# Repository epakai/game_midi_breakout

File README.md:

# Game Midi Breakout

This is my compact hobbyist design for converting game port (DB-15) to MIDI ports. It's made in Kicad. The PCB fits inside a [GOLD-TEK/GTK DH151 connector housing](https://www.taydaelectronics.com/connectors-sockets/d-sub-connectors/d-sub-cover-15-pins-with-short-screw.html).

** Note: This revision is untested. **

The previous revision had incorrect transistor pinouts, but I was able to verify its functionality with a bodge (upside-down transistors). This rev has had minor mods to schematic, and a near-complete re-layout. You're taking a chance I messed something up if you build it without verifying.

Here's what I changed: 

- Schematic
    + Swapped 2N3904 for the correct MMBT3904 transistor (corrects pinout)
    + added capacitors to ground the MIDI cable shield

- PCB layout
    + Caps/Resistors lined up, real nice
    + Silkscreen labels for component references
    + Everything but the OptoIsolator moved around and rerouted

## Pictures

### What you get 

### My first attempt with all it's warts

### 3D renders with most of the components

## BOM

| Quantity | Ref(s) | Value | Mfg Part No. | Description |
|----------|--------|-------|--------------|-------------|
| 1 | J5 | - | DA15PT | GTK 15-pin male D-Sub connector |
| 1 | -  | - | DH151PS/RH | GTK 15-pin D-sub cover |
| 1 | U1 | - | 6N138S | Opto-Isolator 5KV Darl w/Base 8SMD |
| 2 | Q1, Q2 | - | MMBT3904 | NPN Transistor 40V 0.2A SOT23-3 | 
| 1 | D1 | - | 1N4148WSTR | Diode 75V 300MA SOD323 | 
| 3 | C1,C4,C5 | 0.1 µF | CL21F104ZBCNNNC | Ceramic Capacitor 50V 0805 |
| 2 | C2,C3 | 220 pF | CL21B221KBANNNC | Ceramic Capacitor 50V 0805 | 
| 2 | R1, R6 | 220 Ω | CR0805-JW-221ELF | SMD Resistor 5% 1/8W 0805 | 
| 1 | R5 | 270 Ω | CR0805-JW-271ELF | SMD Resistor 5% 1/8W 0805 | 
| 2 | R2, R4 | 2.2 KΩ | CR0805-FX-2201ELF | SMD Resistor 1% 1/8W 0805 | 
| 2 | R3 | 10 KΩ | CR0805-JW-103ELF | SMD Resistor 5% 1/8W 0805 | 

Not included are any cables or MIDI connectors. Be creative. You can connect a pair of cables straight to male or female connectors, or run a single cable to a breakout box with a pair of connectors. Just connect IN or OUT if you like, etc.

## Making it

The D-Sub connector has to be modified before soldering. 

- Remove pins 6 and 7. Small pliers work well, wiggle and pull from the back.
- Pins 5 and 8 need to be cut short to make room for the opto-isolator, but you might wait until after U1 is soldered to check the sizing.

Assembly order:
- D1, Q1, Q2
- C1-C3, R1-R6
- C4, C5
- U1
- Remove and cut pins on J5 (15-pin connector) as described above
- J5
- Attach whatever MIDI cable/sockets you prefer

## The Design

The Output circuit comes from [ESS ES1869 Data Sheet, Page 24](https://www.philscomputerlab.com/uploads/3/7/2/3/37231621/es1869techmanual.pdf#page=24).

The Input circuit is similar, but I found the reference at [Teragon Audio](http://midi.teragonaudio.com/hardware/pc_intfc.htm) to be useful, and I took values and components from there.

The PCB is designed to be a close fit inside the connector housing. Rev 1.0 versions I produced at JLCPCB fit well in my initial build.

## Testing

I tested the adapter with a BTC 1853 Card (ES1868F chipset). I was able to transmit and recieve with a MidiMan MidiSport 1x1 USB adaptor. I also transmitted to a Roland MT-90s.

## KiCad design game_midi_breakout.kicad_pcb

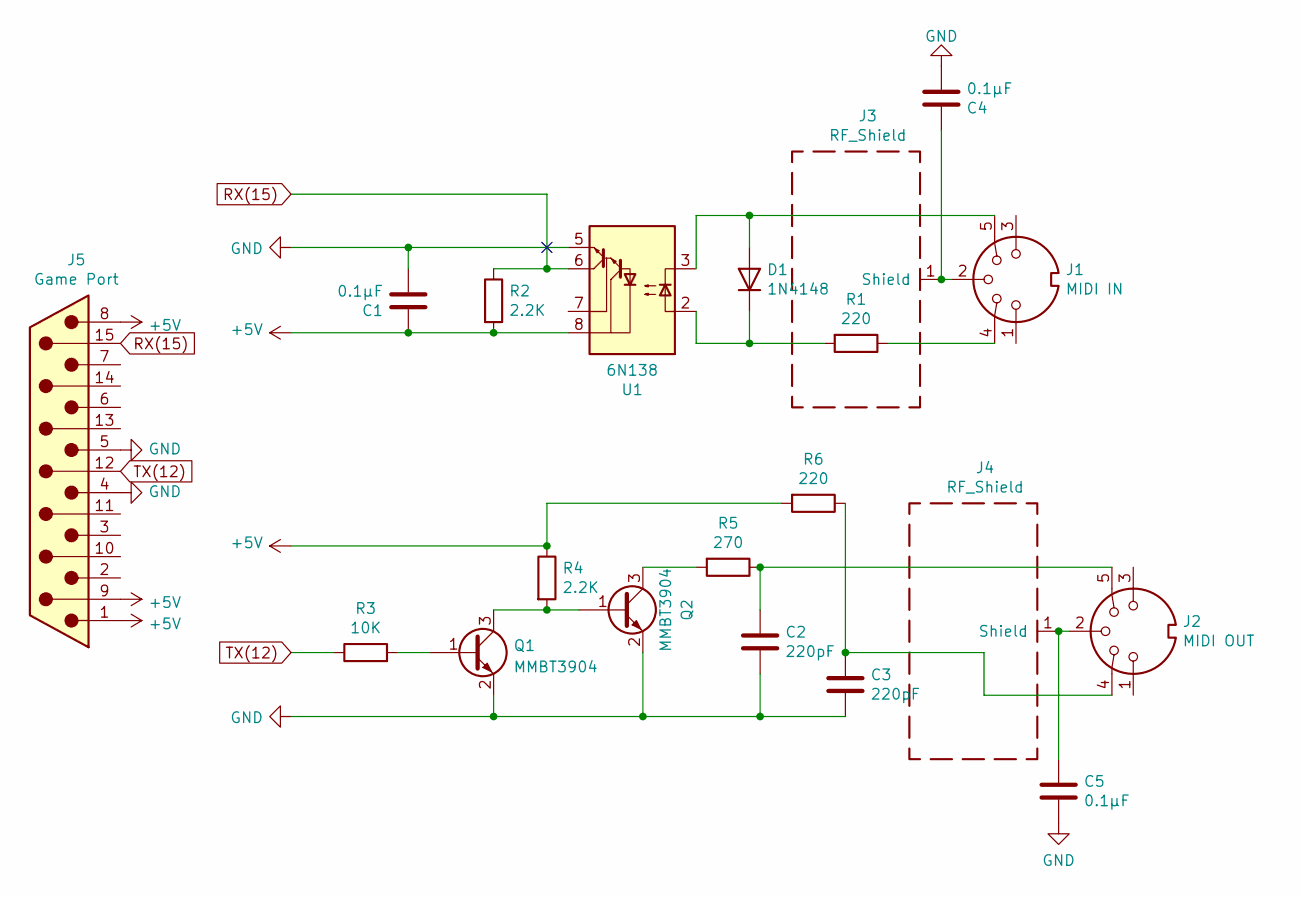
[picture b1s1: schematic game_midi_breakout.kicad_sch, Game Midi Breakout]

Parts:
C1, C4, C5: 0.1μF; C_0805_2012Metric
C2, C3: 220pF; C_0805_2012Metric
D1: 1N4148; D_SOD-323
J1: MIDI IN; midi pads
J2: MIDI OUT; midi pads
J3, J4: RF_Shield
J5: Game Port; DSUB-15_Male_EdgeMount_P2.77mm
Q1, Q2: MMBT3904; SOT-23
R1, R6: 220; R_0805_2012Metric
R2, R4: 2.2K; R_0805_2012Metric
R3: 10K; R_0805_2012Metric
R5: 270; R_0805_2012Metric
U1: 6N138; SMDIP-8_W7.62mm

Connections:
+5V: C1.1, J5.1, J5.8, J5.9, R2.2, R4.1, R6.2, U1.8 (VCC)
GND: C1.2, C2.2, C3.2, C4.2, C5.2, J5.4, J5.5, Q1.2 (E), Q2.2 (E), U1.5 (GND)
unnamed: C2.1, J2.5, R5.1
unnamed: C3.1, J2.4, R6.1
unnamed: D1.1 (K), R1.2, U1.2 (C1)
unnamed: D1.2 (A), J1.5, U1.3 (C2)
unnamed: C4.1, J1.2, J3.1
unnamed: J1.4, R1.1
unnamed: C5.1, J2.2, J4.1
unnamed: Q1.3 (C), Q2.1 (B), R4.2
unnamed: Q1.1 (B), R3.2
unnamed: Q2.3 (C), R5.2
RX(15): J5.15, R2.1, U1.6 (VO2)
TX(12): J5.12, R3.1

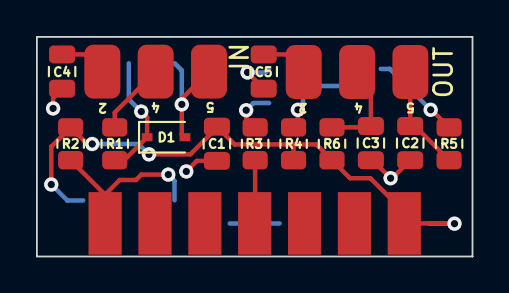
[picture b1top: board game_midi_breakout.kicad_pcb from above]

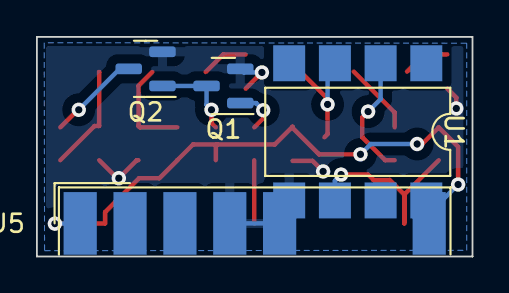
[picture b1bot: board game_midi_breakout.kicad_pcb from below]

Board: 2 copper layers, 24.2 x 12.2 mm, 18 parts (4 on the bottom side), 14 nets.

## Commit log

2023-04-29 Revision 1.1
    This is redisigned PCB after my initial revision sort of worked.
    - New layout
    - More silkscreen
    - Better-er (probably)
2023-04-29 Some cool pictures
    I'm cool too
2023-04-30 Create LICENSE
